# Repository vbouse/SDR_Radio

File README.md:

# SDR_Radio

Software Defined Radio Moto Mod 

A Software Defined Radio (SDR) Moto Mod for analog and digital radio communication: FM, voice, data, IoT networks, spectrum monitoring, security auditing. You can even use your smartphone as a satellite communicator!

This is a repository for the following project:

https://igg.me/at/sdr-mod/x/15776881

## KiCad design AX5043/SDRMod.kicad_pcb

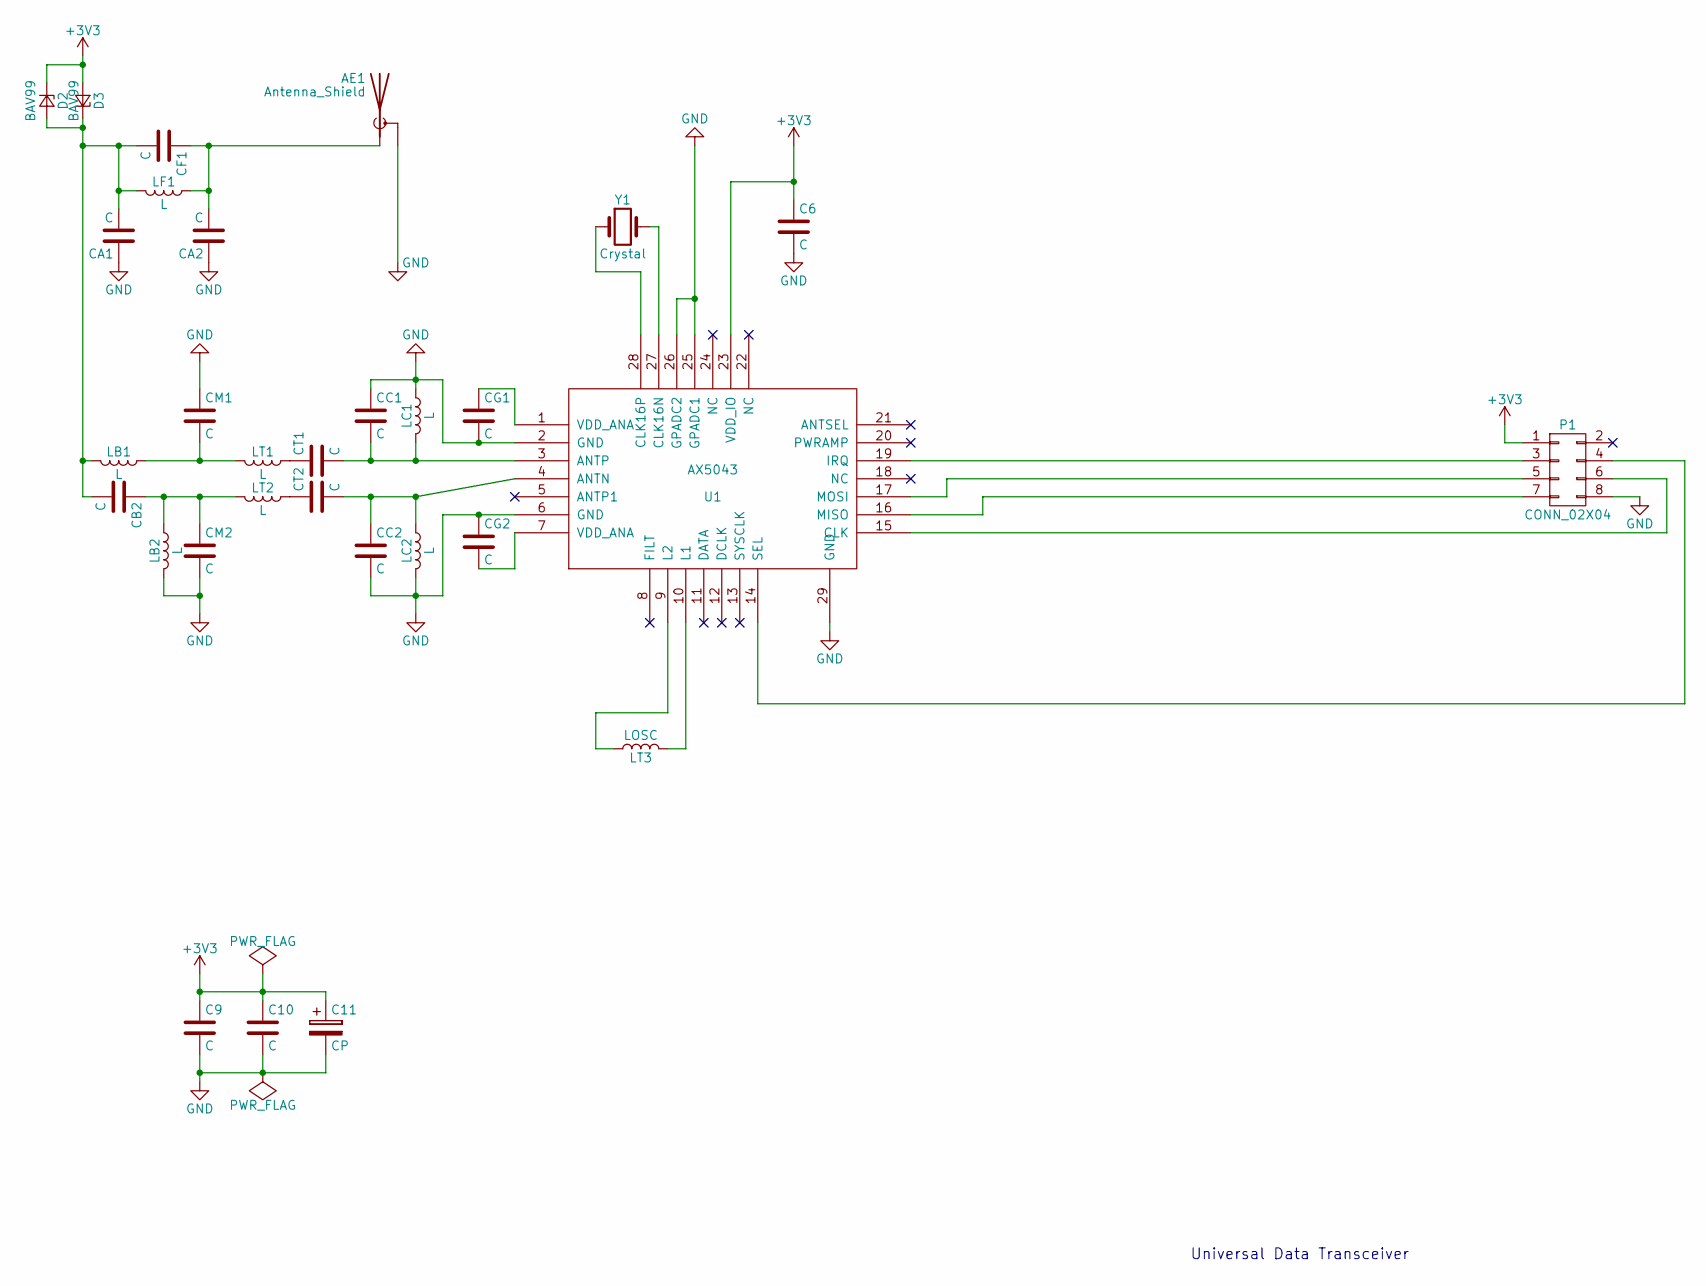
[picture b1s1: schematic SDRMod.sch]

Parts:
AE1: Antenna_Shield; SMB_Straight
C6, C9, C10: C; C_0603_HandSoldering
C11: CP; CP_Elec_3x5.3
CA1, CA2: C; C_0603_HandSoldering
CB2: C; C_0603_HandSoldering
CC1, CC2: C; C_0603_HandSoldering
CF1: C; C_0603_HandSoldering
CG1, CG2: C; C_0603_HandSoldering
CM1, CM2: C; C_0603_HandSoldering
CT1, CT2: C; C_0603_HandSoldering
D2, D3: BAV99; D_SCD80_HandSoldering
LB1, LB2: L; L_0603_HandSoldering
LC1, LC2: L; L_0603_HandSoldering
LF1: L; L_0603_HandSoldering
LT1, LT2: L; L_0603_HandSoldering
LT3: LOSC; L_0603_HandSoldering
P1: CONN_02X04; Pin_Header_Straight_2x04_Pitch2.00mm_SMD
U1: AX5043; QFN-28-1EP_5x6mm_Pitch0.5mm
Y1: Crystal; Crystal_SMD_5032-2pin_5.0x3.2mm_HandSoldering

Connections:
+3V3: C6.1, C9.1, C10.1, C11.1, D2.1 (K), D3.2 (A), P1.1, U1.23 (VDD_IO)
GND: AE1.2 (Shield), C6.2, C9.2, C10.2, C11.2, CA1.1, CA2.1, CC1.1, CC2.2, CG1.2, CG2.1, CM1.1, CM2.2, LB2.2, LC1.1, LC2.2, P1.8, U1.2 (GND), U1.6 (GND), U1.25 (GPADC1), U1.26 (GPADC2), U1.29 (GND)
unnamed: AE1.1 (A), CA2.2, CF1.1, LF1.1
unnamed: CA1.2, CB2.2, CF1.2, D2.2 (A), D3.1 (K), LB1.2, LF1.2
unnamed: CB2.1, CM2.1, LB2.1, LT2.2
unnamed: CC1.2, CT1.2, LC1.2, U1.3 (ANTP)
unnamed: CC2.1, CT2.2, LC2.1, U1.4 (ANTN)
unnamed: CG1.1, U1.1 (VDD_ANA)
unnamed: CG2.2, U1.7 (VDD_ANA)
unnamed: CM1.2, LB1.1, LT1.2
unnamed: CT1.1, LT1.1
unnamed: CT2.1, LT2.1
unnamed: LT3.1, U1.9 (L2)
unnamed: LT3.2, U1.10 (L1)
unnamed: P1.3, U1.19 (IRQ)
unnamed: P1.4, U1.14 (SEL)
unnamed: P1.5, U1.17 (MOSI)
unnamed: P1.6, U1.15 (CLK)
unnamed: P1.7, U1.16 (MISO)
unnamed: U1.27 (CLK16N), Y1.2
unnamed: U1.28 (CLK16P), Y1.1

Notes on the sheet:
Universal Data Transceiver

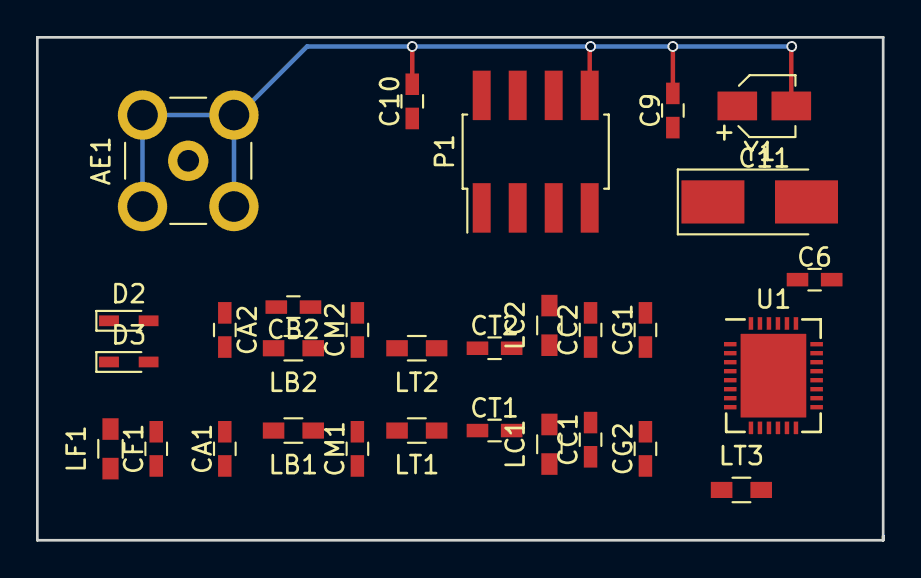
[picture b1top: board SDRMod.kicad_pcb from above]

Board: 2 copper layers, 47.0 x 27.9 mm, 30 parts (0 on the bottom side), 21 nets.

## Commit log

2017-02-24 all files added
2017-03-01 the correct project uploaded (with FET based level shifters)
2017-03-01 .bck files deleted
2017-03-01 AX5043 and level shifter splitted into two projects, IR removed
